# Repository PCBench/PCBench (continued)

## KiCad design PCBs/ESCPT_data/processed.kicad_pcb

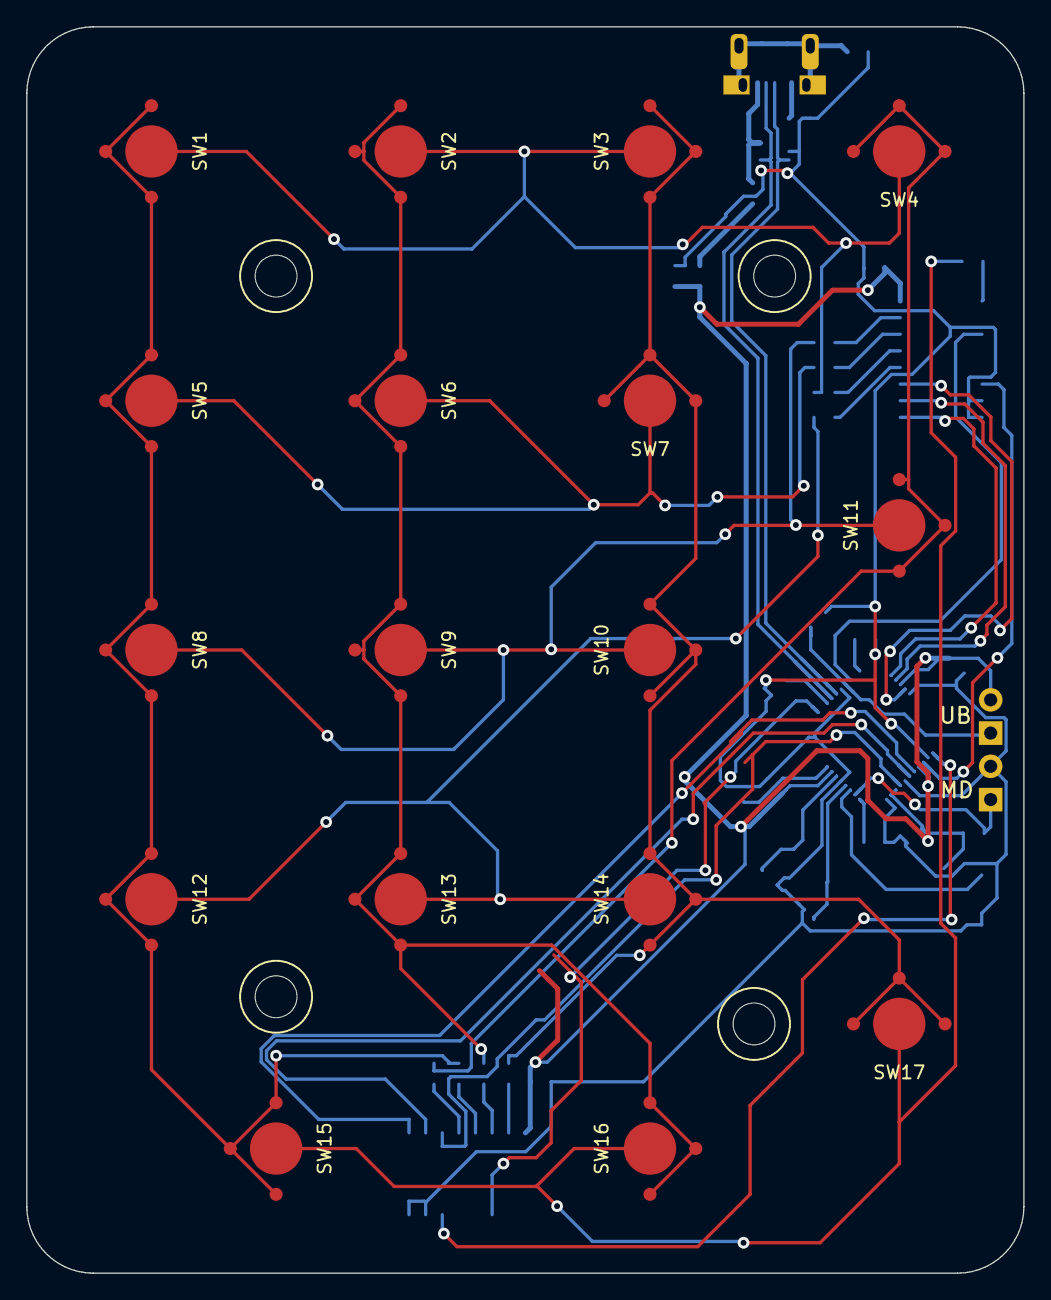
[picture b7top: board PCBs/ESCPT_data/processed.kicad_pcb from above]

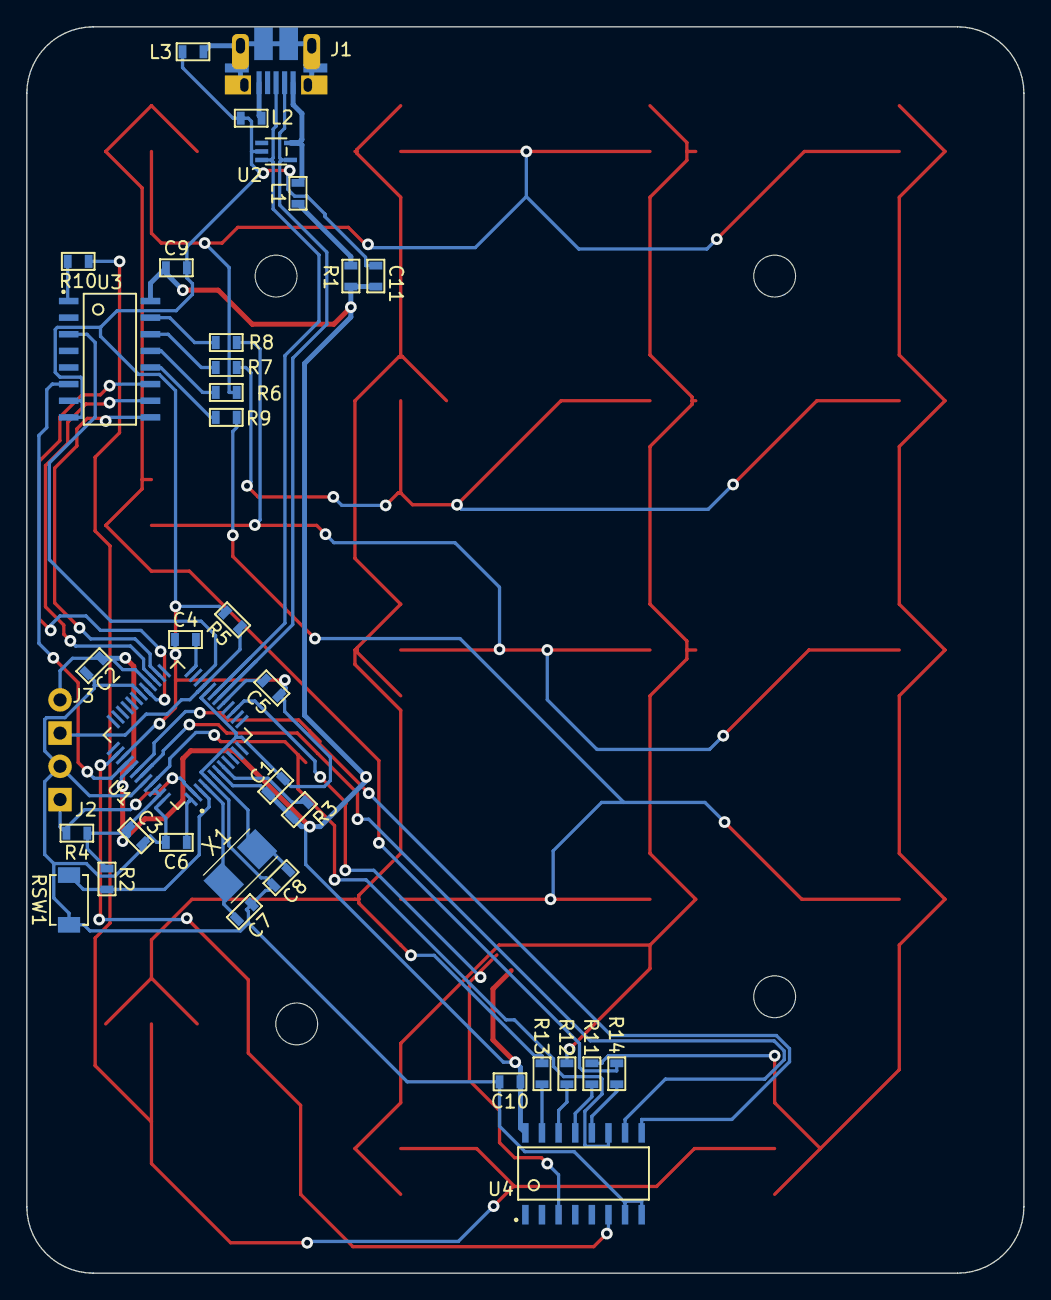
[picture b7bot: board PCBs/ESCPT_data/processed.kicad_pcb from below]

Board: 2 copper layers, 76.2 x 95.2 mm, 58 parts (37 on the bottom side), 45 nets.

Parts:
C1, C2, C3, C9, C10: 100n; 0603_1608
C4: 10n; 0603_1608
C5: 330n; 0603_1608
C6, C11: 4u7; 0603_1608
C7, C8: 4p; 0603_1608
J1: MicroB; 10103594
J2, J3: CON2; J2
L1, L2, L3: INDUCTOR2; 0603_1608
R1: Polyswitch; 0603_1608
R2, R4: 4K7; 0603_1608_R
R3, R5: 10K; 0603_1608_R
R6, R7, R8, R9, R10, R11, R12, R13, R14: 470; 0603_1608_R
RSW1: SWITCH; TD_85XU
SR1, SR2, SR3, SR4: M3; M3NP
SW1, SW2, SW3, SW4, SW5, SW6, SW7, SW8, SW9, SW10, SW11, SW12, SW13, SW14, SW15, SW16, SW17: ESC_Pad_D
U1: R5F5231XAXFL; LQFP48-0.5
U2: DF5A6.8; SOT353
U3, U4: 74HC4051; SOIC16
X1: 12MHz; Crystal_5032

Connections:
/COL: U1.15, U4.3
/COL0: R11.1, SW1.2, SW5.2, SW8.2, SW12.2, SW15.2
/COL1: R12.1, SW2.2, SW6.2, SW9.2, SW13.2, SW16.2
/COL2: R13.1, SW3.2, SW7.2, SW10.2, SW14.2, SW17.2
/COL3: R14.1, SW4.2, SW11.2
/COL_A: U1.45, U4.11
/COL_B: U1.43, U4.10
/COL_C: U1.42, U4.9
/COL_INH: U1.38, U4.6
/MD: J2.1, R4.2, U1.2
/RESET: R2.2, RSW1.1, U1.3
/ROW: U1.22, U3.3
/ROW1: R6.1, SW1.1, SW2.1, SW3.1, SW4.1
/ROW2: R7.1, SW5.1, SW6.1, SW7.1
/ROW3: R8.1, SW8.1, SW9.1, SW10.1, SW11.1
/ROW4: R9.1, SW12.1, SW13.1, SW14.1
/ROW5: R10.1, SW15.1, SW16.1, SW17.1
/ROW_A: U1.29, U3.11
/ROW_B: U1.27, U3.10
/ROW_C: U1.26, U3.9
/ROW_INH: U1.40, U3.6
/TSCAP: C4.2, U1.24
/UB: J3.1, R5.1, U1.21
/USB_DM: J1.2, U1.18, U2.4
/USB_DP: J1.3, U1.19, U2.3
/VBUS: J1.1, L1.2, U2.5
GND: C1.2, C2.2, C3.2, C4.1, C5.1, C6.2, C7.2, C8.2, C9.2, C10.2, C11.2, J2.2, L2.1, L3.1, R5.2, RSW1.2, U1.5, U1.20, U1.30, U1.39, U1.44, U1.48, U2.2, U3.7, U3.8, U4.7, U4.8
unnamed: C5.2, U1.17
unnamed: C6.1, U1.1
unnamed: C7.1, U1.4, X1.2
unnamed: C8.1, U1.6, X1.1
unnamed: J1.5, L2.2
unnamed: J1.6, L3.2
unnamed: L1.1, R1.1
unnamed: R3.1, U1.8
unnamed: R6.2, U3.13
unnamed: R7.2, U3.14
unnamed: R8.2, U3.15
unnamed: R9.2, U3.12
unnamed: R10.2, U3.1
unnamed: R11.2, U4.13
unnamed: R12.2, U4.14
unnamed: R13.2, U4.15
unnamed: R14.2, U4.12
VCC: C1.1, C2.1, C3.1, C9.1, C10.1, C11.1, J3.2, R1.2, R2.1, R3.2, R4.1, U1.7, U1.28, U1.41, U1.46, U1.47, U3.16, U4.16
